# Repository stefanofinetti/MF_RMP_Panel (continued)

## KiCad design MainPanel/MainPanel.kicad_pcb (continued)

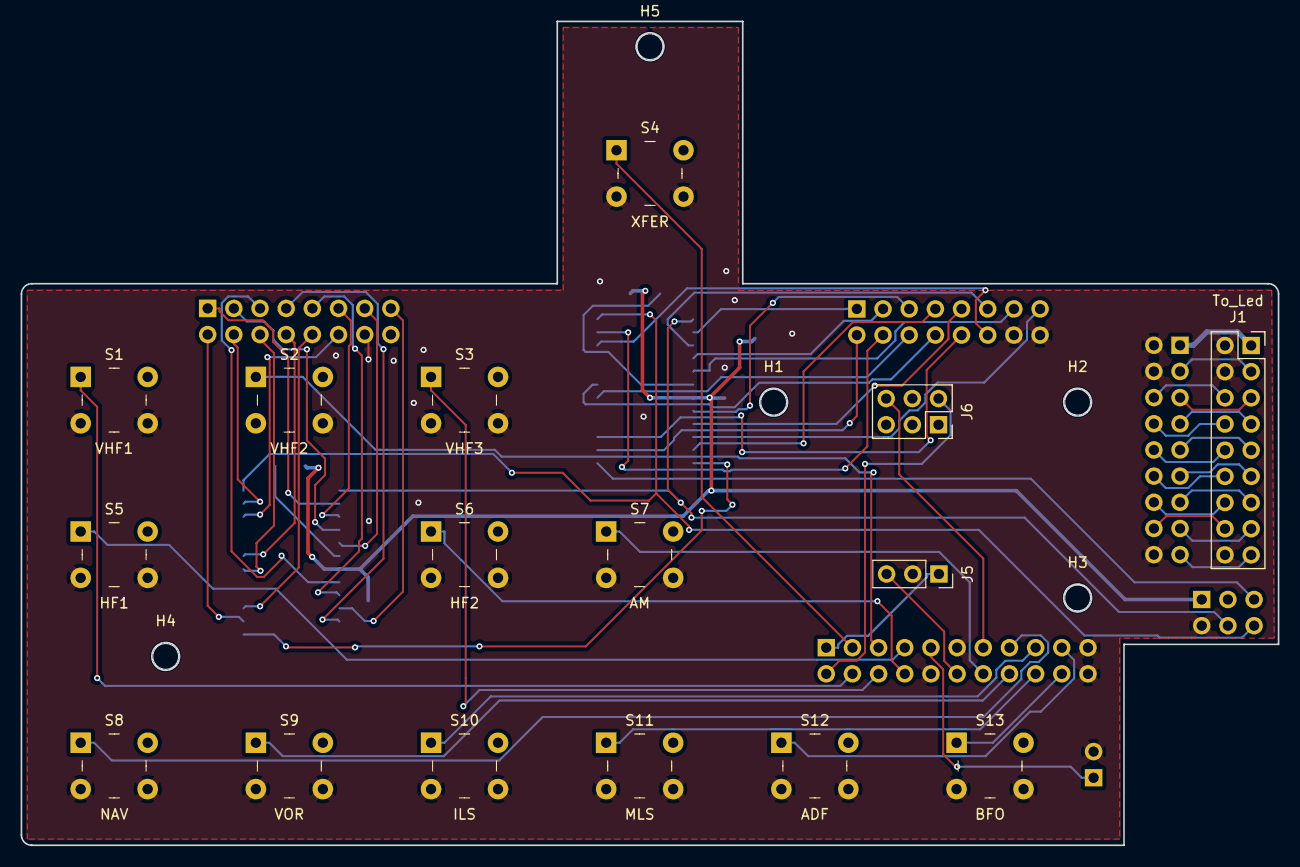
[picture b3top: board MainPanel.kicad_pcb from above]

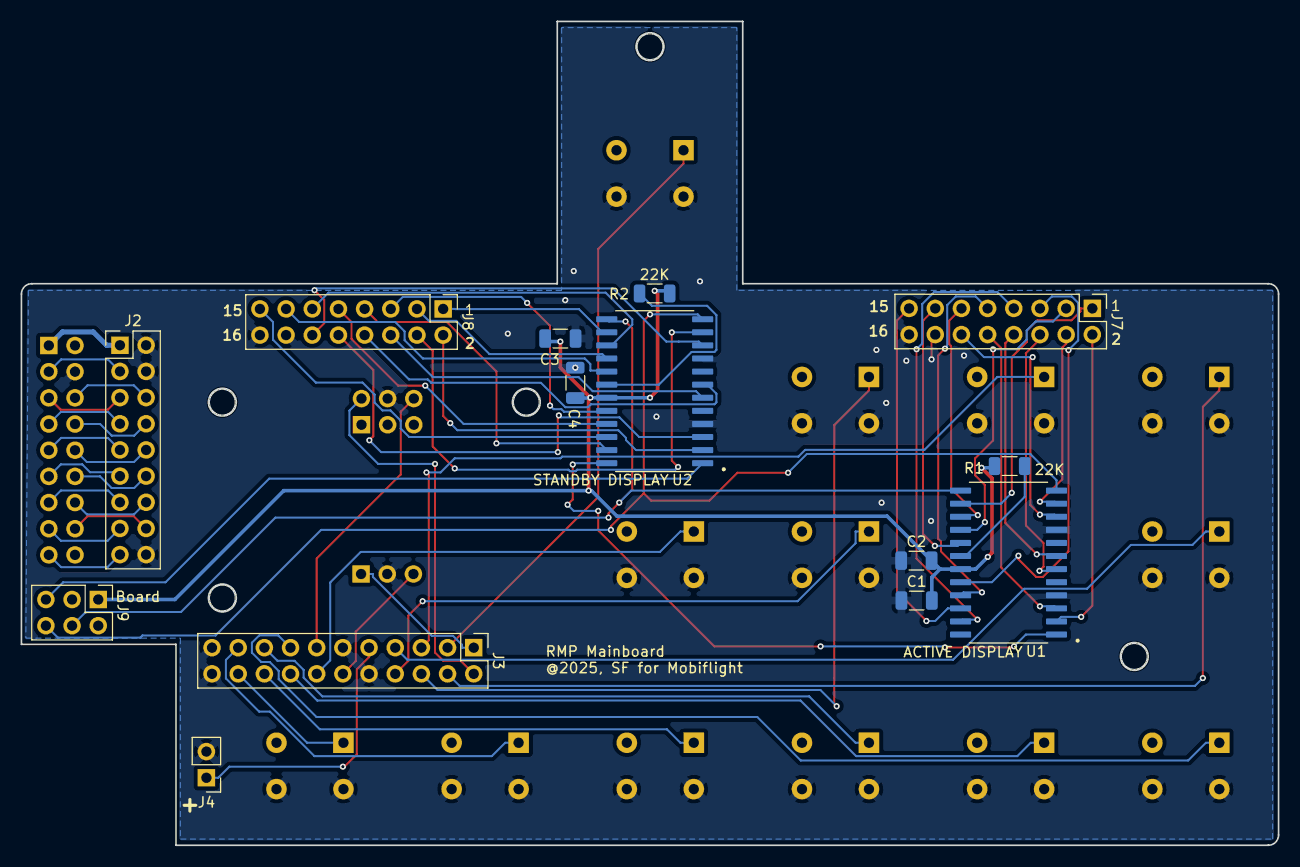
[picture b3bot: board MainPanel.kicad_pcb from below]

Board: 2 copper layers, 122.0 x 79.9 mm, 35 parts (14 on the bottom side), 69 nets.

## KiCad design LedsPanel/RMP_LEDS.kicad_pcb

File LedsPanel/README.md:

# RMP LedsPanel

The lighting board, right behind the front panel: the backlight of the
legends and the thirteen key lights. It plugs straight into the MainPanel.

* **PCB:** 122 × 80 mm, 2 layers, 1.6 mm, GND poured on both sides.
* **Fixing:** six M2.5 holes.
* **Parts:** 113. The backlight resistors and J1 are on the bottom.
* **Status:** built and in use. ERC, DRC and schematic parity are clean.

| Top: the panel side | Bottom: resistors and J1 |
|---|---|
|  |  |

Rendered by KiCad from the board file. The bottom is seen from below, so it
is mirrored against the top.

## Connector

| Ref | What | Goes to |
|---|---|---|
| J1 | Header 2 × 9, on the bottom | Plugs into the MainPanel's J1. 1 `+12V`, 2 / 4 / 18 GND, 3 backlight PWM, 5–17 the key LEDs |

## Backlight

69 orange 0805 LEDs, chosen to match the brightness of the Airbus panels,
on `+12V`:

* D1–D65: thirteen strings of five, each with its 75 Ω (R3–R15);
* D79–D82: one string of four, with R29, 75 Ω.

Every string returns to `LED_RETURN`, switched to GND by Q1, an IRLZ44N
(logic-level N-MOSFET, D2PAK). Its gate is driven by the backlight PWM
(D6) through R1, 100 Ω, with R2, 10 kΩ, pulling it down: with the PWM at 0
or the MobiFlight Connector closed, the backlight is off.

The string of four has one LED fewer across the same 75 Ω, so it carries
more current than the strings of five.

## Key lights

D66–D78, 3 mm flat-top LEDs, one in each key. The anode is driven straight
by the MCU pin through J1; the cathode goes to GND through 200 Ω
(R16–R28).

| D66 | D67 | D68 | D69 | D70 | D71 | D72 | D73 | D74 | D75 | D76 | D77 | D78 |
|---|---|---|---|---|---|---|---|---|---|---|---|---|
| VHF1 | VHF2 | VHF3 | HF1 | HF2 | AM | NAV | VOR | ILS | MLS | ADF | BFO | SEL |

The key lights are not dimmed. On the aircraft they follow the ANN LT
switch, apart from the backlight; a separate dimmer for them is being
considered.

## Assembly notes

* Everything is sized for hand soldering: 0805 LEDs, 1206 resistors.
* LED polarity, values and pin 1 are on the silkscreen.

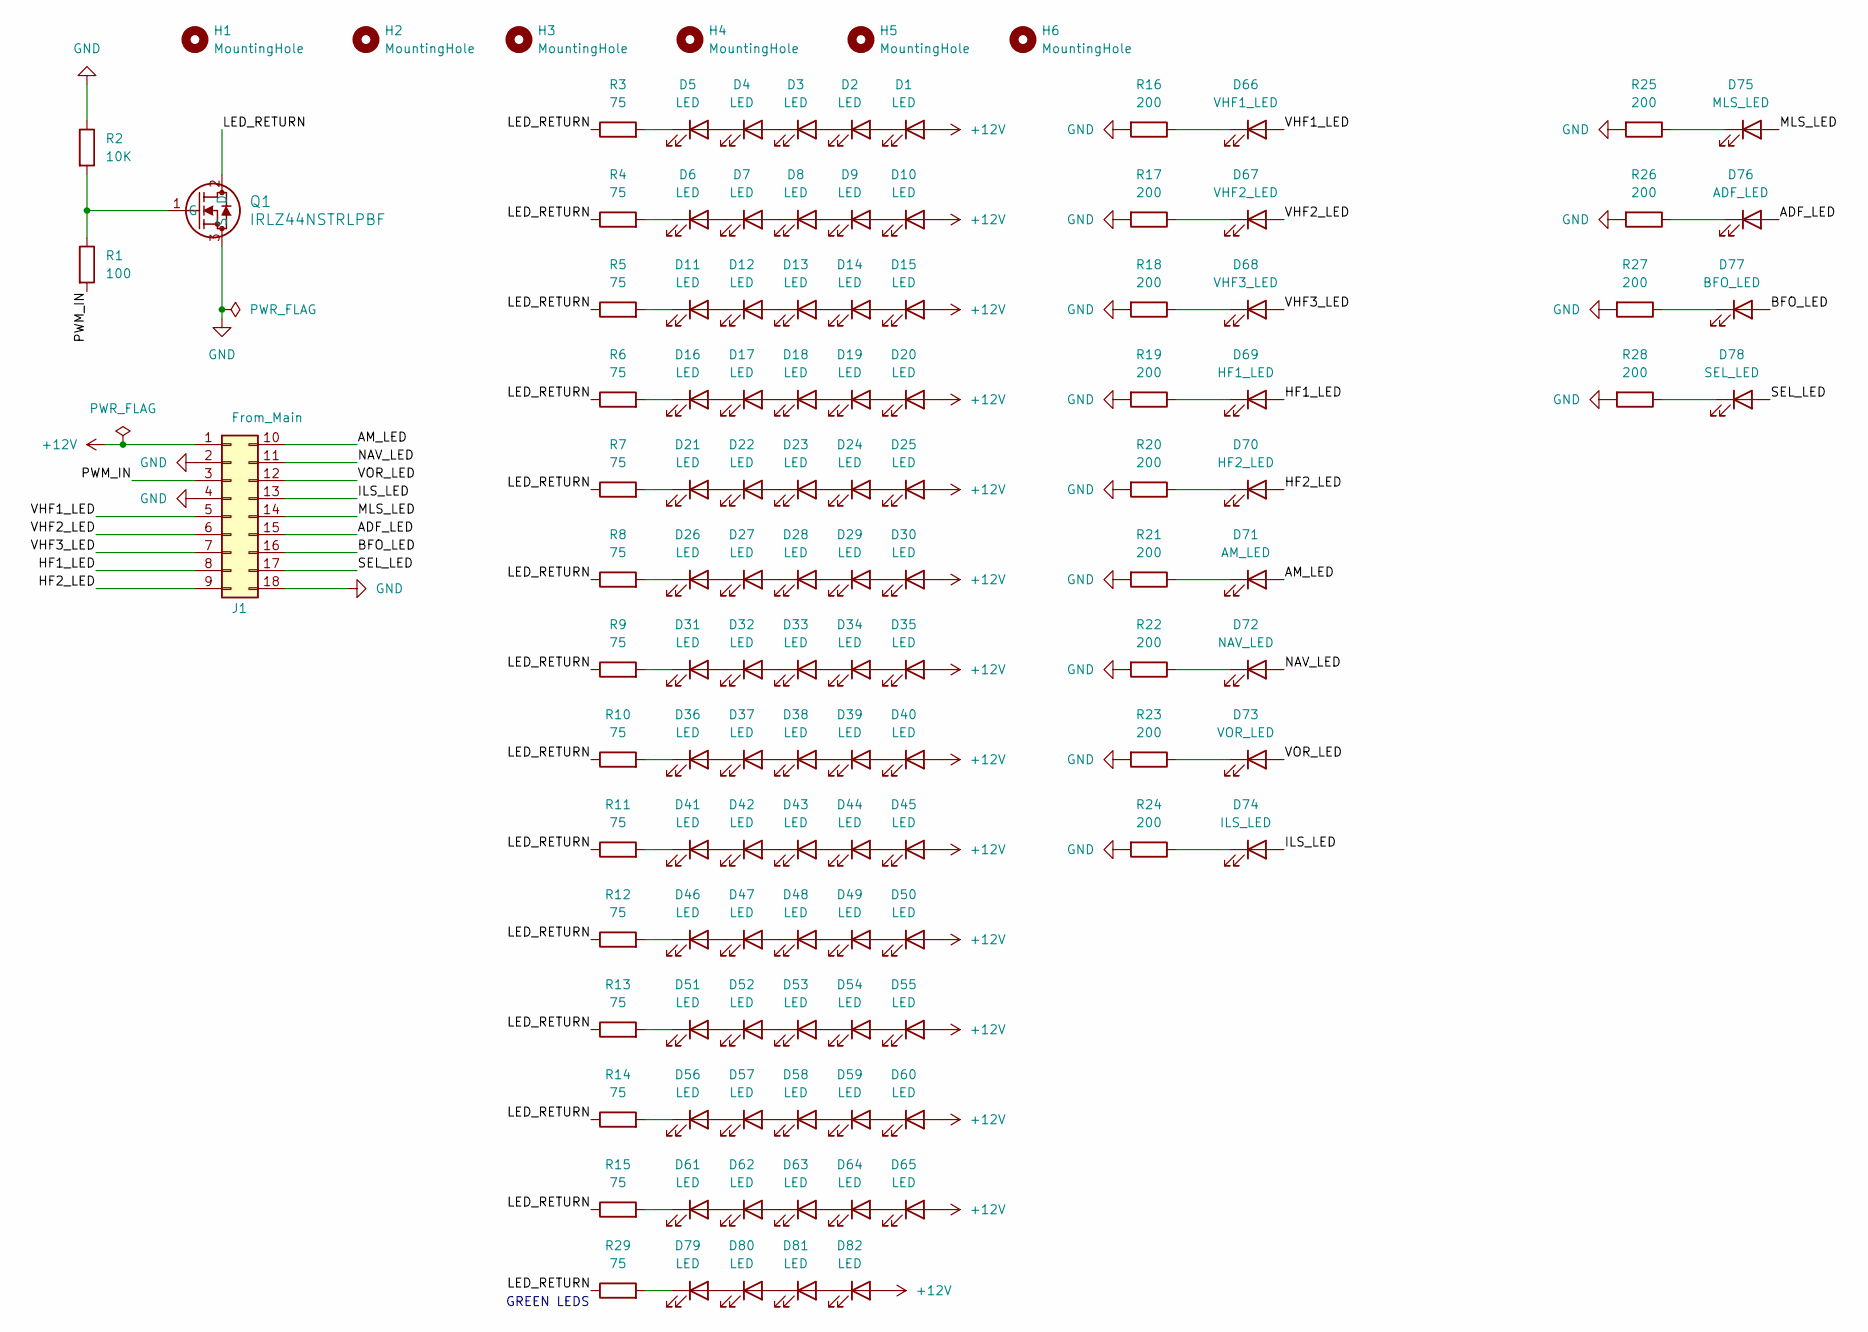
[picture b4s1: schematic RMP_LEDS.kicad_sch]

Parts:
D1, D2, D3, D4, D5, D6, D7, D8, D9, D10, D11, D12, D13, D14, D15, D16, D17, D18, D19, D20, D21, D22, D23, D24, D25, D26, D27, D28, D29, D30, D31, D32, D33, D34, D35, D36, D37, D38, D39, D40, D41, D42, D43, D44, D45, D46, D47, D48, D49, D50, D51, D52, D53, D54, D55, D56, D57, D58, D59, D60, D61, D62, D63, D64, D65, D79, D80, D81, D82: LED; LED_0805_2012Metric_Pad1.15x1.40mm_HandSolder
D66: VHF1_LED; LED_D3.0mm_FlatTop
D67: VHF2_LED; LED_D3.0mm_FlatTop
D68: VHF3_LED; LED_D3.0mm_FlatTop
D69: HF1_LED; LED_D3.0mm_FlatTop
D70: HF2_LED; LED_D3.0mm_FlatTop
D71: AM_LED; LED_D3.0mm_FlatTop
D72: NAV_LED; LED_D3.0mm_FlatTop
D73: VOR_LED; LED_D3.0mm_FlatTop
D74: ILS_LED; LED_D3.0mm_FlatTop
D75: MLS_LED; LED_D3.0mm_FlatTop
D76: ADF_LED; LED_D3.0mm_FlatTop
D77: BFO_LED; LED_D3.0mm_FlatTop
D78: SEL_LED; LED_D3.0mm_FlatTop
H1, H2, H3, H4, H5, H6: MountingHole; MountingHole_2.7mm_M2.5
J1: From_Main; PinHeader_2x09_P2.54mm_Vertical
Q1: IRLZ44NSTRLPBF; NMOSGDS_D2PAK_INF
R1: 100; R_1206_3216Metric_Pad1.30x1.75mm_HandSolder
R2: 10K; R_1206_3216Metric_Pad1.30x1.75mm_HandSolder
R3, R4, R5, R6, R7, R8, R9, R10, R11, R12, R13, R14, R15, R29: 75; R_1206_3216Metric_Pad1.30x1.75mm_HandSolder
R16, R17, R18, R19, R20, R21, R22, R23, R24, R25, R26, R27, R28: 200; R_1206_3216Metric_Pad1.30x1.75mm_HandSolder

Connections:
+12V: D1.2 (A), D10.2 (A), D15.2 (A), D20.2 (A), D25.2 (A), D30.2 (A), D35.2 (A), D40.2 (A), D45.2 (A), D50.2 (A), D55.2 (A), D60.2 (A), D65.2 (A), D82.2 (A), J1.1
/ADF_LED: D76.2 (A), J1.15
/AM_LED: D71.2 (A), J1.10
/BFO_LED: D77.2 (A), J1.16
/HF1_LED: D69.2 (A), J1.8
/HF2_LED: D70.2 (A), J1.9
/ILS_LED: D74.2 (A), J1.13
/LED_RETURN: Q1.2 (D), R3.1, R4.1, R5.1, R6.1, R7.1, R8.1, R9.1, R10.1, R11.1, R12.1, R13.1, R14.1, R15.1, R29.1
/MLS_LED: D75.2 (A), J1.14
/NAV_LED: D72.2 (A), J1.11
/PWM_IN: J1.3, R1.2
/SEL_LED: D78.2 (A), J1.17
/VHF1_LED: D66.2 (A), J1.5
/VHF2_LED: D67.2 (A), J1.6
/VHF3_LED: D68.2 (A), J1.7
/VOR_LED: D73.2 (A), J1.12
GND: J1.2, J1.4, J1.18, Q1.3 (S), R2.1, R16.2, R17.2, R18.2, R19.2, R20.2, R21.2, R22.2, R23.2, R24.2, R25.2, R26.2, R27.2, R28.2
unnamed: D1.1 (K), D2.2 (A)
unnamed: D2.1 (K), D3.2 (A)
unnamed: D3.1 (K), D4.2 (A)
unnamed: D4.1 (K), D5.2 (A)
unnamed: D5.1 (K), R3.2
unnamed: D6.2 (A), D7.1 (K)
unnamed: D6.1 (K), R4.2
unnamed: D7.2 (A), D8.1 (K)
unnamed: D8.2 (A), D9.1 (K)
unnamed: D9.2 (A), D10.1 (K)
unnamed: D11.2 (A), D12.1 (K)
unnamed: D11.1 (K), R5.2
unnamed: D12.2 (A), D13.1 (K)
unnamed: D13.2 (A), D14.1 (K)
unnamed: D14.2 (A), D15.1 (K)
unnamed: D16.2 (A), D17.1 (K)
unnamed: D16.1 (K), R6.2
unnamed: D17.2 (A), D18.1 (K)
unnamed: D18.2 (A), D19.1 (K)
unnamed: D19.2 (A), D20.1 (K)
unnamed: D21.2 (A), D22.1 (K)
unnamed: D21.1 (K), R7.2
unnamed: D22.2 (A), D23.1 (K)
unnamed: D23.2 (A), D24.1 (K)
unnamed: D24.2 (A), D25.1 (K)
unnamed: D26.2 (A), D27.1 (K)
unnamed: D26.1 (K), R8.2
unnamed: D27.2 (A), D28.1 (K)
unnamed: D28.2 (A), D29.1 (K)
unnamed: D29.2 (A), D30.1 (K)
unnamed: D31.2 (A), D32.1 (K)
unnamed: D31.1 (K), R9.2
unnamed: D32.2 (A), D33.1 (K)
unnamed: D33.2 (A), D34.1 (K)
unnamed: D34.2 (A), D35.1 (K)
unnamed: D36.2 (A), D37.1 (K)
unnamed: D36.1 (K), R10.2
unnamed: D37.2 (A), D38.1 (K)
unnamed: D38.2 (A), D39.1 (K)
unnamed: D39.2 (A), D40.1 (K)
unnamed: D41.2 (A), D42.1 (K)
unnamed: D41.1 (K), R11.2
unnamed: D42.2 (A), D43.1 (K)
unnamed: D43.2 (A), D44.1 (K)
unnamed: D44.2 (A), D45.1 (K)
unnamed: D46.2 (A), D47.1 (K)
unnamed: D46.1 (K), R12.2
unnamed: D47.2 (A), D48.1 (K)
unnamed: D48.2 (A), D49.1 (K)
unnamed: D49.2 (A), D50.1 (K)
unnamed: D51.2 (A), D52.1 (K)
unnamed: D51.1 (K), R13.2
unnamed: D52.2 (A), D53.1 (K)
unnamed: D53.2 (A), D54.1 (K)
unnamed: D54.2 (A), D55.1 (K)
unnamed: D56.2 (A), D57.1 (K)
unnamed: D56.1 (K), R14.2
unnamed: D57.2 (A), D58.1 (K)
unnamed: D58.2 (A), D59.1 (K)
unnamed: D59.2 (A), D60.1 (K)
unnamed: D61.2 (A), D62.1 (K)
unnamed: D61.1 (K), R15.2
unnamed: D62.2 (A), D63.1 (K)
unnamed: D63.2 (A), D64.1 (K)
unnamed: D64.2 (A), D65.1 (K)
unnamed: D66.1 (K), R16.1
unnamed: D67.1 (K), R17.1
unnamed: D68.1 (K), R18.1
unnamed: D69.1 (K), R19.1
unnamed: D70.1 (K), R20.1
unnamed: D71.1 (K), R21.1
unnamed: D72.1 (K), R22.1
unnamed: D73.1 (K), R23.1
unnamed: D74.1 (K), R24.1
unnamed: D75.1 (K), R25.1
unnamed: D76.1 (K), R26.1
unnamed: D77.1 (K), R27.1
unnamed: D78.1 (K), R28.1
unnamed: D79.2 (A), D80.1 (K)
unnamed: D79.1 (K), R29.2
unnamed: D80.2 (A), D81.1 (K)
unnamed: D81.2 (A), D82.1 (K)
unnamed: Q1.1 (G), R1.1, R2.2

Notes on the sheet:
GREEN LEDS

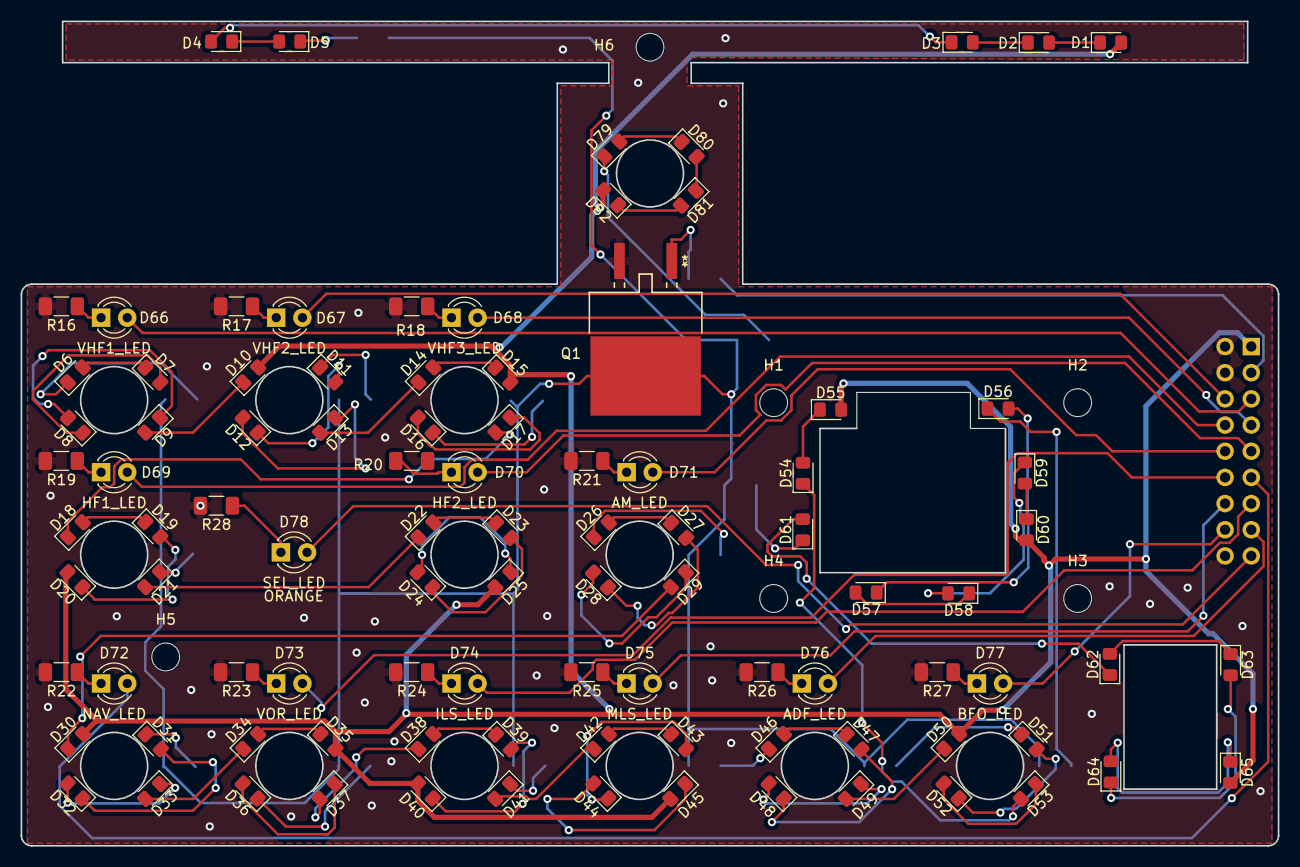
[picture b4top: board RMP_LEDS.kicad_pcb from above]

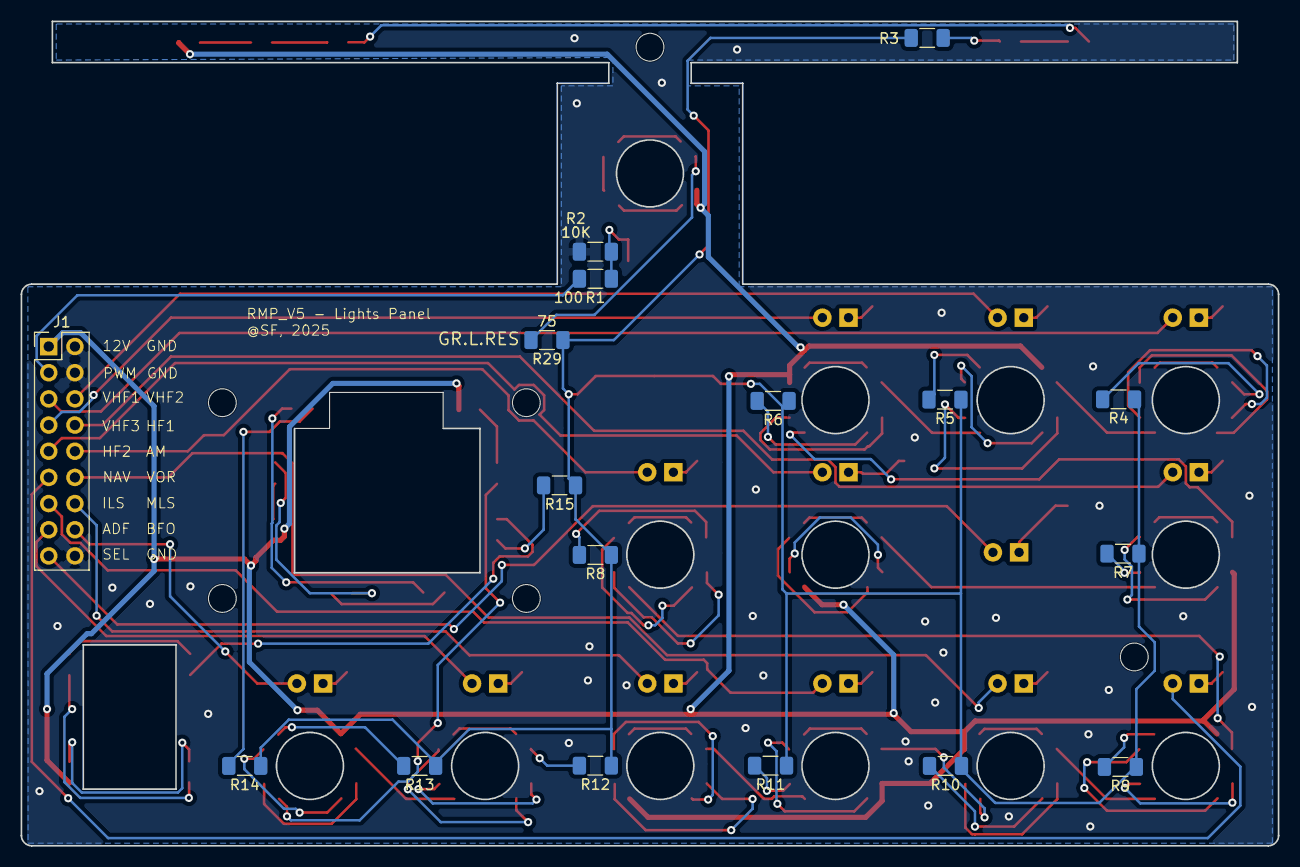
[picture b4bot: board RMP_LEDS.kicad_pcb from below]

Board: 2 copper layers, 122.0 x 80.0 mm, 119 parts (17 on the bottom side), 100 nets.

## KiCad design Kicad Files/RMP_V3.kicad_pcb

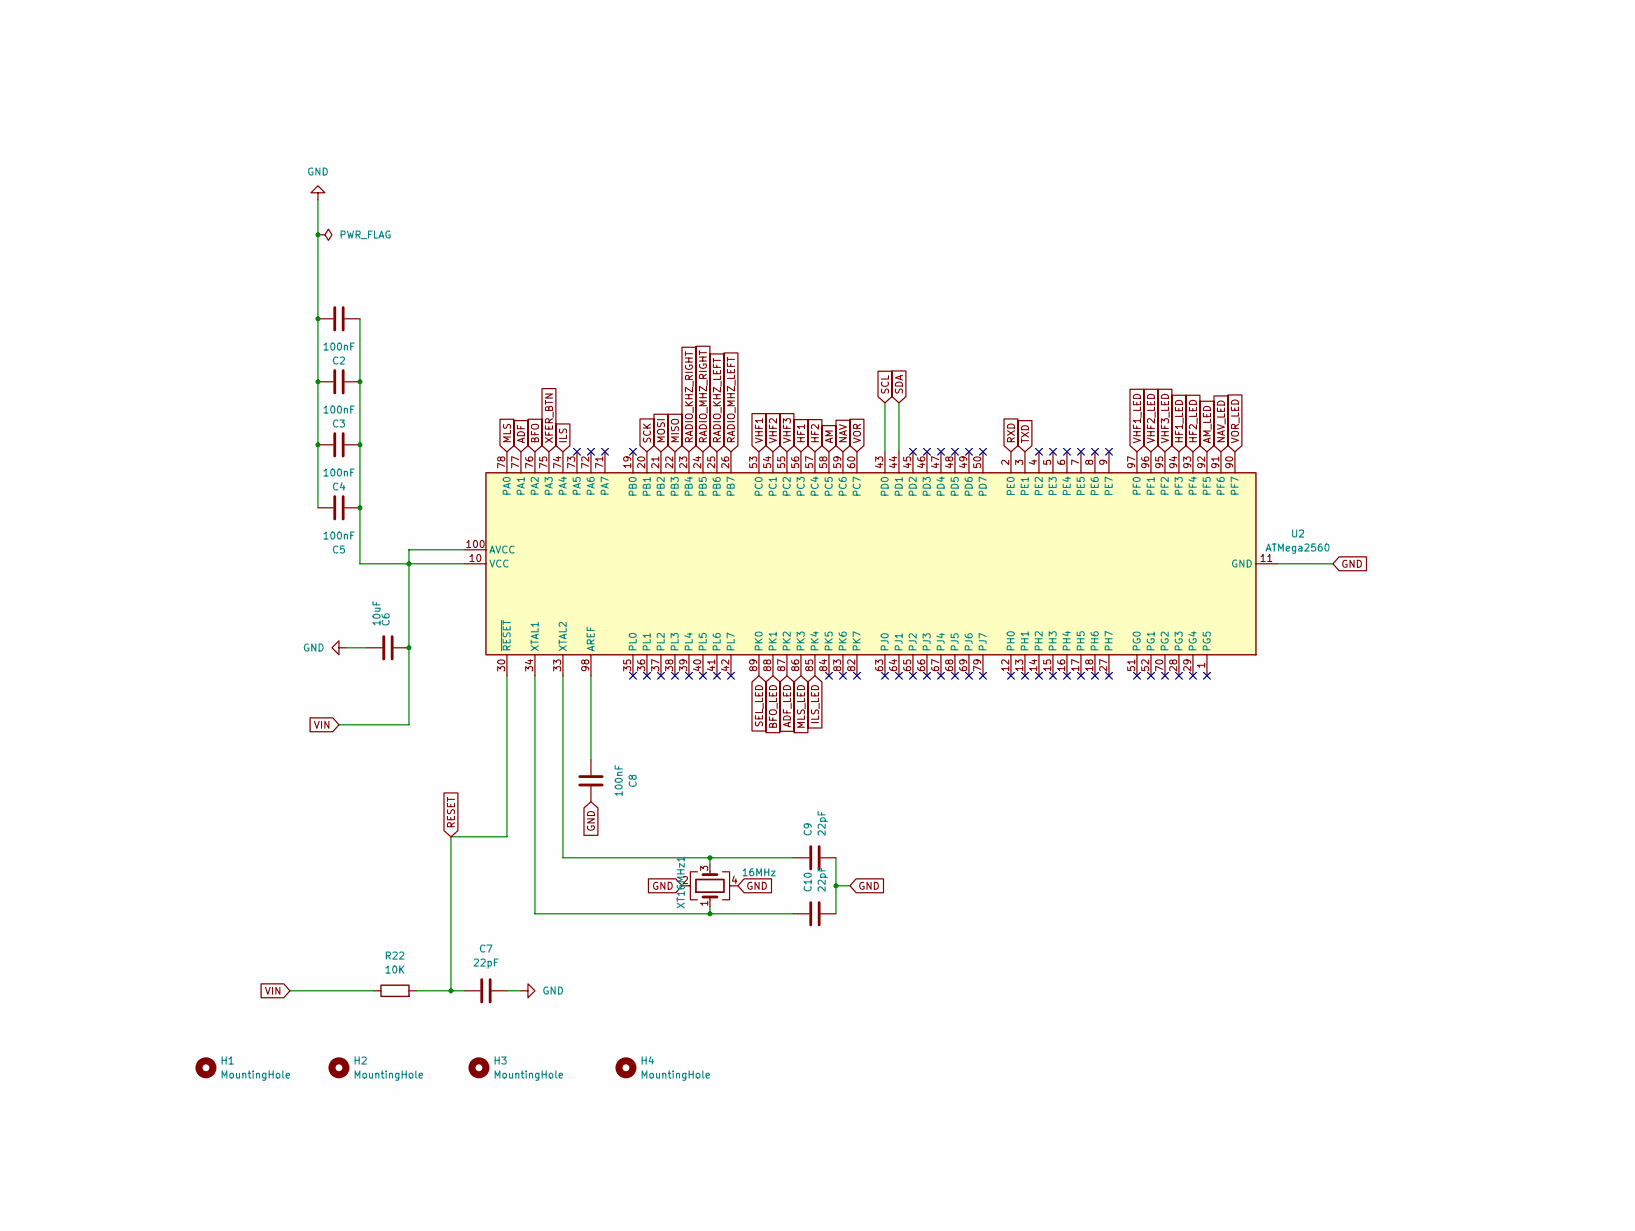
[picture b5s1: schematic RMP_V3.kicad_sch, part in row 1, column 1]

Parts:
C2, C3, C4, C5, C8: 100nF; C_1206_3216Metric_Pad1.33x1.80mm_HandSolder
C6: 10uF; C_1206_3216Metric_Pad1.33x1.80mm_HandSolder
C7, C9, C10: 22pF; C_1206_3216Metric_Pad1.33x1.80mm_HandSolder
H1, H2, H3, H4: MountingHole; MountingHole_3.2mm_M3
R22: 10K; R_1206_3216Metric_Pad1.30x1.75mm_HandSolder
U2: ATMega2560; TQFP-100_14x14mm_P0.5mm
XT16MHz1: 16MHz; Crystal_SMD_EuroQuartz_MJ-4Pin_5.0x3.2mm_HandSoldering

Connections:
ADF: U2.77 (PA1); also elsewhere on the board
ADF_LED: U2.87 (PK2); also elsewhere on the board
AM: U2.58 (PC5); also elsewhere on the board
AM_LED: U2.92 (PF5); also elsewhere on the board
BFO: U2.76 (PA2); also elsewhere on the board
BFO_LED: U2.88 (PK1); also elsewhere on the board
GND: C2.2, C3.2, C4.2, C5.2, C6.2, C7.2, C8.2, C9.2, C10.2, U2.11 (GND), U2.32 (GND), U2.62 (GND), U2.81 (GND), U2.99 (GND), XT16MHz1.2, XT16MHz1.4; also elsewhere on the board
HF1: U2.56 (PC3); also elsewhere on the board
HF1_LED: U2.94 (PF3); also elsewhere on the board
HF2: U2.57 (PC4); also elsewhere on the board
HF2_LED: U2.93 (PF4); also elsewhere on the board
ILS: U2.74 (PA4); also elsewhere on the board
ILS_LED: U2.85 (PK4); also elsewhere on the board
MISO: U2.22 (PB3); also elsewhere on the board
MLS: U2.78 (PA0); also elsewhere on the board
MLS_LED: U2.86 (PK3); also elsewhere on the board
MOSI: U2.21 (PB2); also elsewhere on the board
NAV: U2.59 (PC6); also elsewhere on the board
NAV_LED: U2.91 (PF6); also elsewhere on the board
unnamed: C8.1, U2.98 (AREF)
unnamed: C10.1, U2.34 (XTAL1), XT16MHz1.1
unnamed: C9.1, U2.33 (XTAL2), XT16MHz1.3
RADIO_KHZ_LEFT: U2.25 (PB6); also elsewhere on the board
RADIO_KHZ_RIGHT: U2.23 (PB4); also elsewhere on the board
RADIO_MHZ_LEFT: U2.26 (PB7); also elsewhere on the board
RADIO_MHZ_RIGHT: U2.24 (PB5); also elsewhere on the board
RESET: C7.1, R22.2, U2.30 (~RESET); also elsewhere on the board
RXD: U2.2 (PE0); also elsewhere on the board
SCK: U2.20 (PB1); also elsewhere on the board
SCL: U2.43 (PD0); also elsewhere on the board
SDA: U2.44 (PD1); also elsewhere on the board
SEL_LED: U2.89 (PK0); also elsewhere on the board
TXD: U2.3 (PE1); also elsewhere on the board
VHF1: U2.53 (PC0); also elsewhere on the board
VHF1_LED: U2.97 (PF0); also elsewhere on the board
VHF2: U2.54 (PC1); also elsewhere on the board
VHF2_LED: U2.96 (PF1); also elsewhere on the board
VHF3: U2.55 (PC2); also elsewhere on the board
VHF3_LED: U2.95 (PF2); also elsewhere on the board
VIN: C2.1, C3.1, C4.1, C5.1, C6.1, R22.1, U2.10 (VCC), U2.31 (VCC), U2.61 (VCC), U2.80 (VCC), U2.100 (AVCC); also elsewhere on the board
VOR: U2.60 (PC7); also elsewhere on the board
VOR_LED: U2.90 (PF7); also elsewhere on the board
XFER_BTN: U2.75 (PA3); also elsewhere on the board

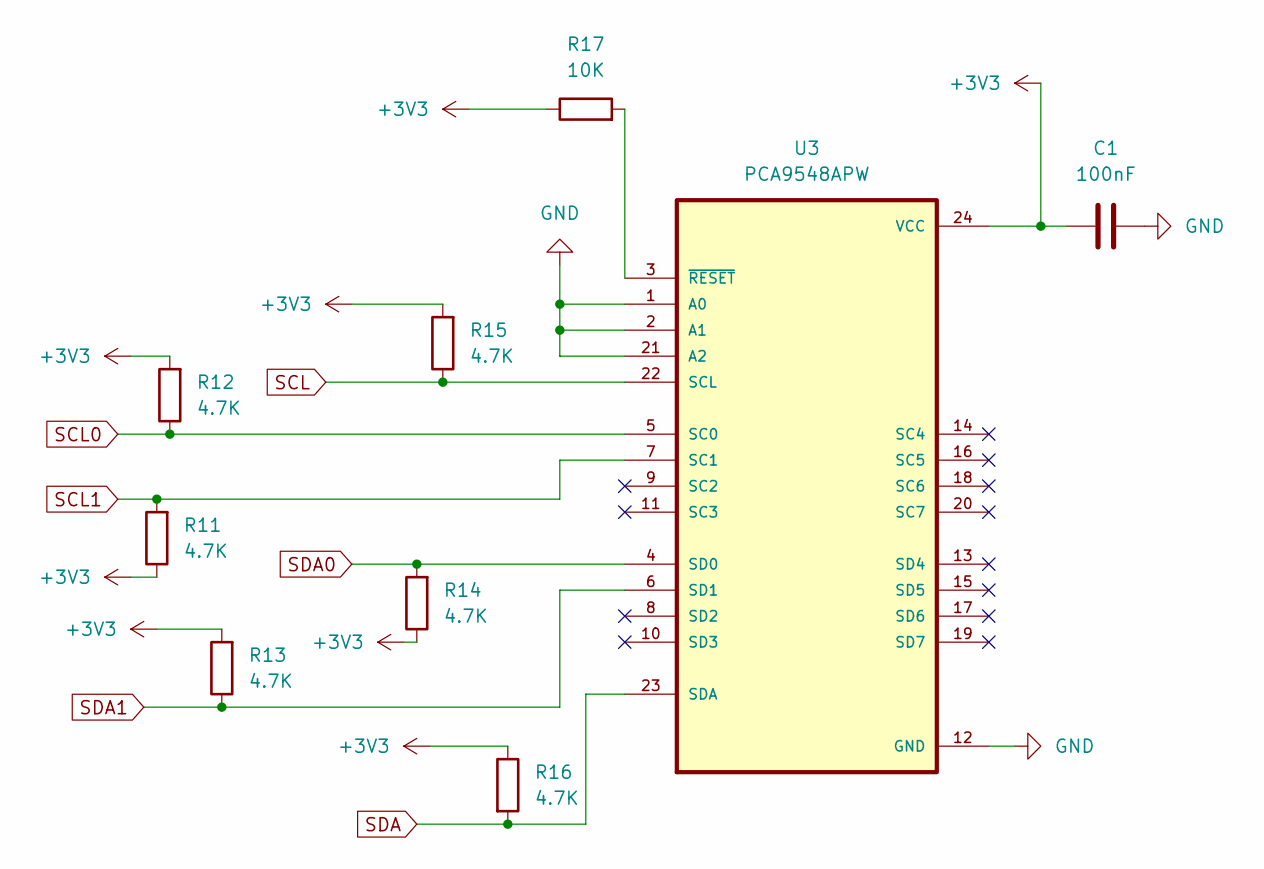
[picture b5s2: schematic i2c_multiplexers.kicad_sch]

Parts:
C1: 100nF; C_1206_3216Metric_Pad1.33x1.80mm_HandSolder
R11, R12, R13, R14, R15, R16: 4.7K; R_1206_3216Metric_Pad1.30x1.75mm_HandSolder
R17: 10K; R_1206_3216Metric_Pad1.30x1.75mm_HandSolder
U3: PCA9548APW; SOP65P640X120-24N

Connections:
+3V3: C1.1, R11.1, R12.2, R13.2, R14.1, R15.2, R16.1, R17.1, U3.24 (VCC); also elsewhere on the board
GND: C1.2, U3.1 (A0), U3.2 (A1), U3.12 (GND), U3.21 (A2); also elsewhere on the board
unnamed: R17.2, U3.3 (~RESET)
SCL: R15.1, U3.22 (SCL); also elsewhere on the board
SCL0: R12.1, U3.5 (SC0); also elsewhere on the board
SCL1: R11.2, U3.7 (SC1); also elsewhere on the board
SDA: R16.2, U3.23 (SDA); also elsewhere on the board
SDA0: R14.2, U3.4 (SD0); also elsewhere on the board
SDA1: R13.1, U3.6 (SD1); also elsewhere on the board

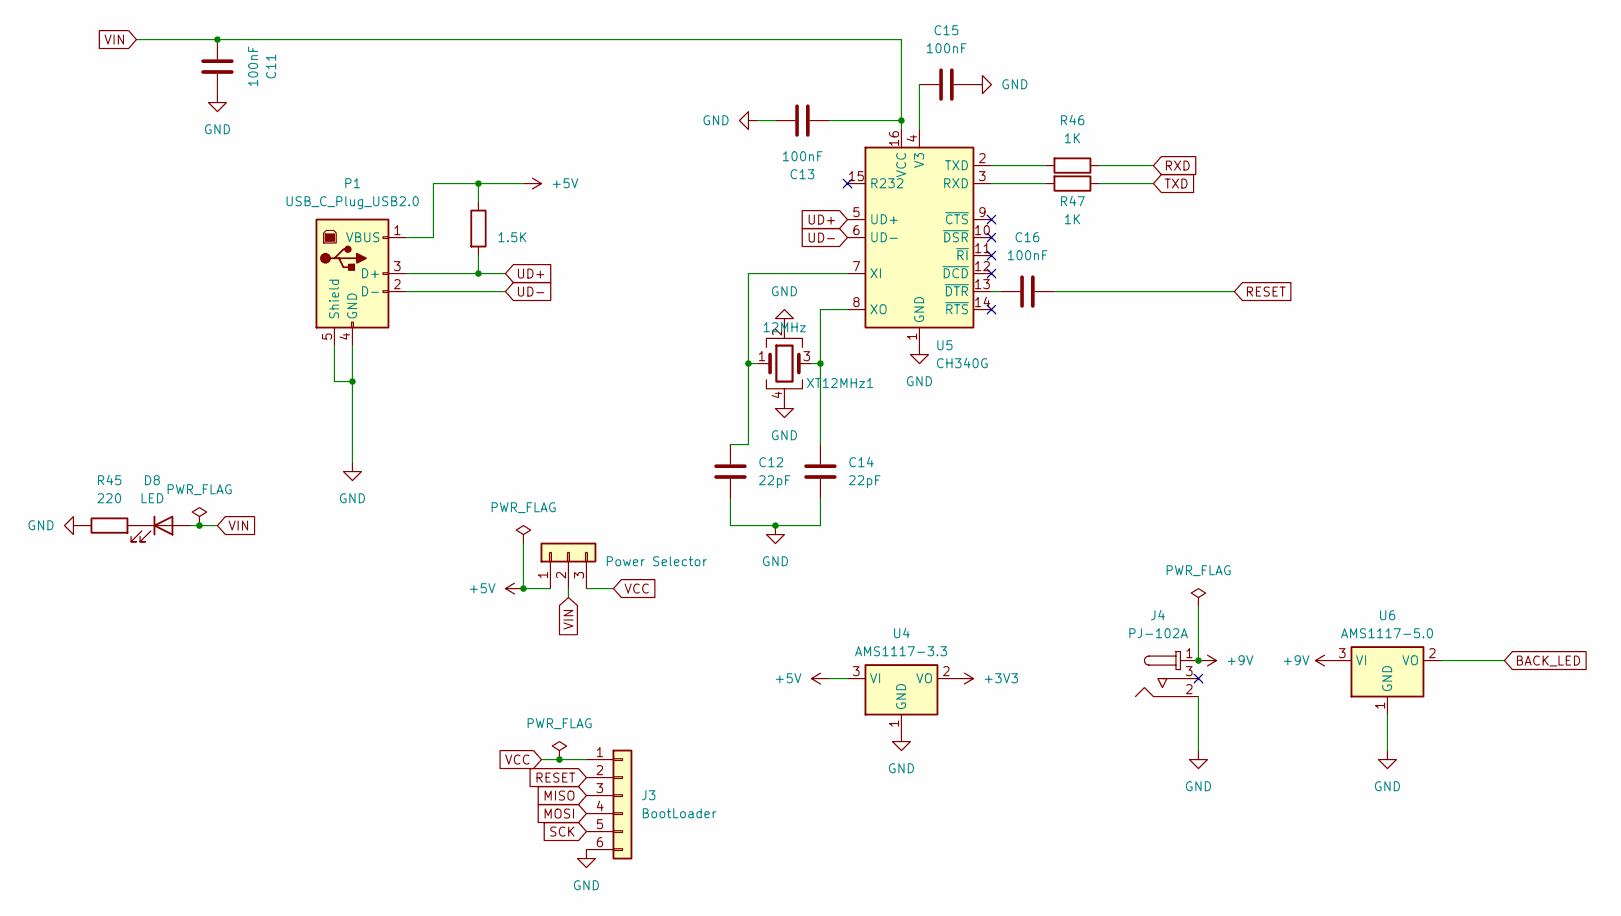
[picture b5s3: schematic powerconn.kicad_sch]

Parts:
C11, C13, C15, C16: 100nF; C_1206_3216Metric_Pad1.33x1.80mm_HandSolder
C12, C14: 22pF; C_1206_3216Metric_Pad1.33x1.80mm_HandSolder
D8: LED; LED_1206_3216Metric_Pad1.42x1.75mm_HandSolder
J3: BootLoader; PinHeader_1x06_P2.54mm_Vertical
J4: PJ-102A; Barrel_Jack_5.5mmODx2.1mmID_PJ-102A; MPN PJ-102A; Digi-Key_PN CP-102A-ND
JP1: Power Selector; PinHeader_1x03_P2.54mm_Vertical
P1: USB_C_Plug_USB2.0; USB_B_OST_USB-B1HSxx_Horizontal
R45: 220; R_1206_3216Metric_Pad1.30x1.75mm_HandSolder
R46, R47: 1K; R_1206_3216Metric_Pad1.30x1.75mm_HandSolder
R48: 1.5K; R_1206_3216Metric_Pad1.30x1.75mm_HandSolder
U4: AMS1117-3.3; SOT-223-3_TabPin2
U5: CH340G; SOIC-16_3.9x9.9mm_P1.27mm
U6: AMS1117-5.0; SOT-223-3_TabPin2
XT12MHz1: 12MHz; Crystal_SMD_EuroQuartz_MJ-4Pin_5.0x3.2mm_HandSoldering

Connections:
+3V3: U4.2 (VO); also elsewhere on the board
+5V: JP1.1, P1.1 (VBUS), R48.1, U4.3 (VI)
+9V: J4.1, U6.3 (VI)
BACK_LED: U6.2 (VO); also elsewhere on the board
GND: C11.2, C12.1, C13.2, C14.1, C15.2, J3.6, J4.2, P1.4 (GND), P1.5 (Shield), R45.1, U4.1 (GND), U5.1 (GND), U6.1 (GND), XT12MHz1.2, XT12MHz1.4; also elsewhere on the board
MISO: J3.3; also elsewhere on the board
MOSI: J3.4; also elsewhere on the board
unnamed: D8.1 (K), R45.2
unnamed: R47.2, U5.3 (RXD)
unnamed: R46.2, U5.2 (TXD)
unnamed: C15.1, U5.4 (V3)
unnamed: C12.2, U5.7 (XI), XT12MHz1.1
unnamed: C14.2, U5.8 (XO), XT12MHz1.3
unnamed: C16.1, U5.13 (~DTR)
RESET: C16.2, J3.2; also elsewhere on the board
RXD: R46.1; also elsewhere on the board
SCK: J3.5; also elsewhere on the board
TXD: R47.1; also elsewhere on the board
UD+: P1.3 (D+), R48.2, U5.5 (UD+)
UD-: P1.2 (D-), U5.6 (UD-)
VCC: J3.1, JP1.3
VIN: C11.1, C13.1, D8.2 (A), JP1.2, U5.16 (VCC); also elsewhere on the board

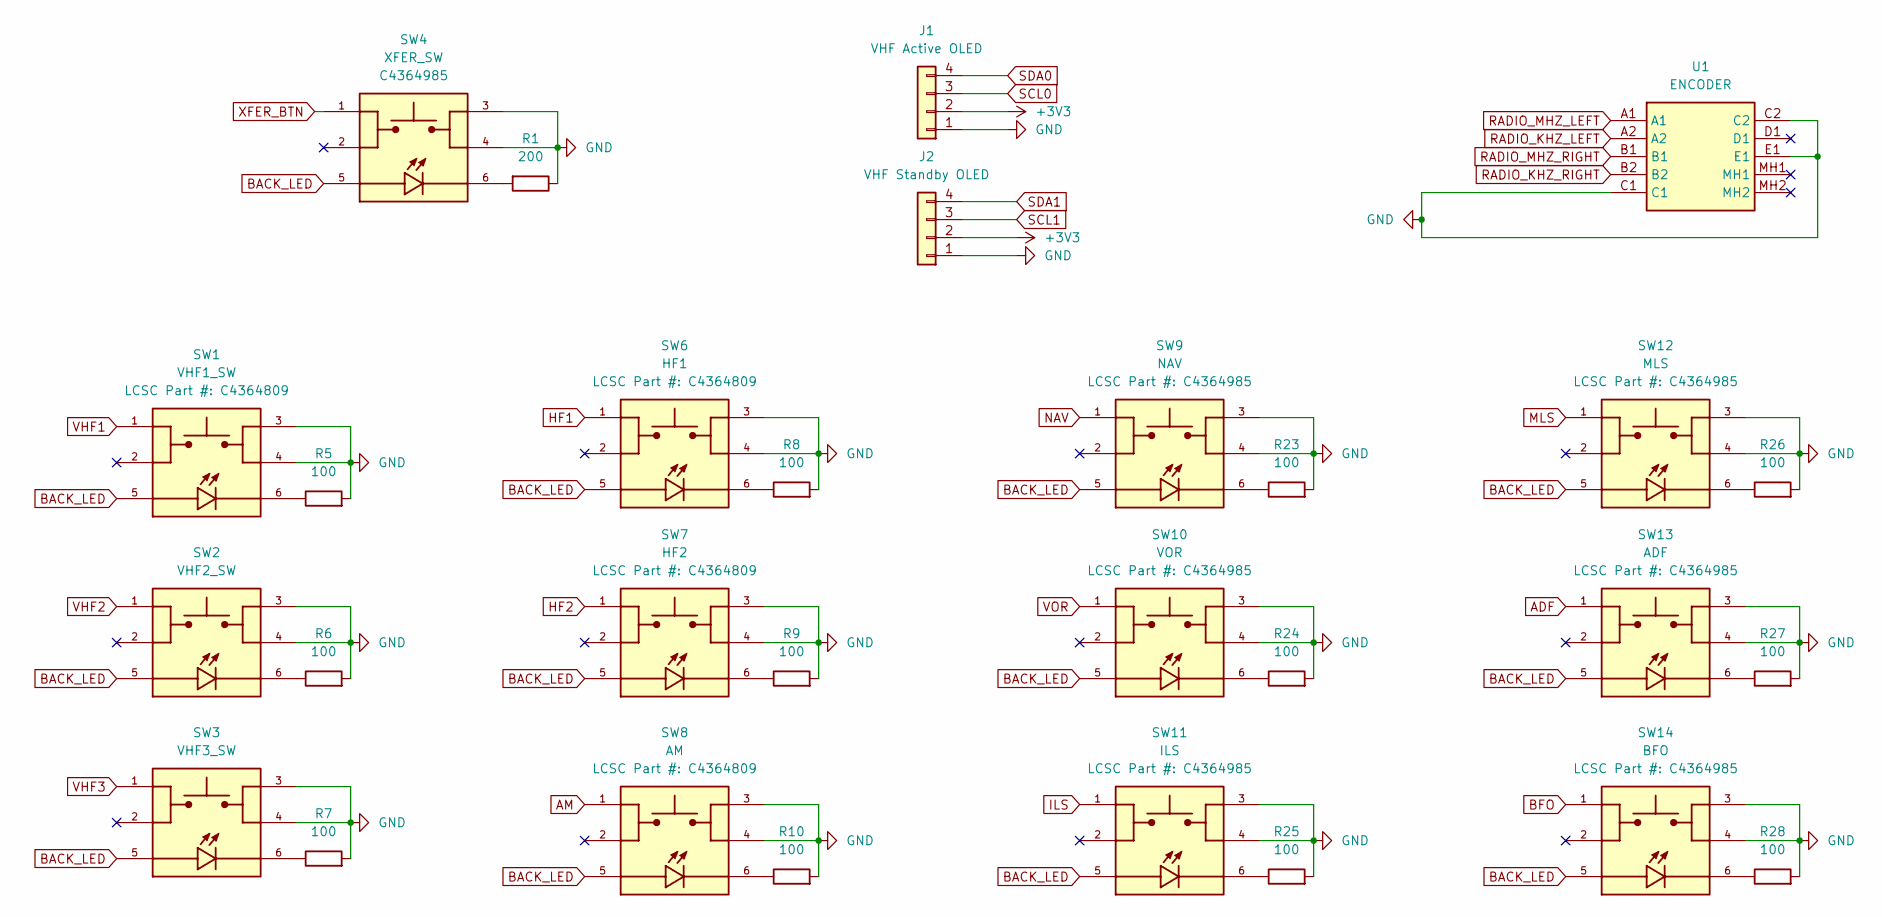
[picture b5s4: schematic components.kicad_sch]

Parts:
J1: VHF Active OLED; PinSocket_1x04_P2.54mm_Vertical
J2: VHF Standby OLED; PinSocket_1x04_P2.54mm_Vertical
R1: 200; R_1206_3216Metric_Pad1.30x1.75mm_HandSolder
R5, R6, R7, R8, R9, R10, R23, R24, R25, R26, R27, R28: 100; R_1206_3216Metric_Pad1.30x1.75mm_HandSolder
SW1: VHF1_SW; SW_TL3240F260R; PARTREV D; LCSC Part # C4364809
SW2: VHF2_SW; SW_TL3240F260R; PARTREV D; LCSC Part # C4364809
SW3: VHF3_SW; SW_TL3240F260R; PARTREV D; LCSC Part # C4364809
SW4: XFER_SW; SW_TL3240F260R; PARTREV D; LCSC Part # C4364985
SW6: HF1; SW_TL3240F260R; PARTREV D; LCSC Part # C4364809
SW7: HF2; SW_TL3240F260R; PARTREV D; LCSC Part # C4364809
SW8: AM; SW_TL3240F260R; PARTREV D; LCSC Part # C4364809
SW9: NAV; SW_TL3240F260R; PARTREV D; LCSC Part # C4364985
SW10: VOR; SW_TL3240F260R; PARTREV D; LCSC Part # C4364985
SW11: ILS; SW_TL3240F260R; PARTREV D; LCSC Part # C4364985
SW12: MLS; SW_TL3240F260R; PARTREV D; LCSC Part # C4364985
SW13: ADF; SW_TL3240F260R; PARTREV D; LCSC Part # C4364985
SW14: BFO; SW_TL3240F260R; PARTREV D; LCSC Part # C4364985
U1: ENCODER; EC11EBB24C03; Manufacturer_Part_Number EC11EBB24C03; Mouser Part Number 688-EC11EBB24C03

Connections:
+3V3: J1.2, J2.2; also elsewhere on the board
ADF: SW13.1; also elsewhere on the board
AM: SW8.1; also elsewhere on the board
BACK_LED: SW1.5, SW2.5, SW3.5, SW4.5, SW6.5, SW7.5, SW8.5, SW9.5, SW10.5, SW11.5, SW12.5, SW13.5, SW14.5; also elsewhere on the board
BFO: SW14.1; also elsewhere on the board
GND: J1.1, J2.1, R1.1, R5.2, R6.2, R7.2, R8.2, R9.2, R10.2, R23.2, R24.2, R25.2, R26.2, R27.2, R28.2, SW1.3, SW1.4, SW2.3, SW2.4, SW3.3, SW3.4, SW4.3, SW4.4, SW6.3, SW6.4, SW7.3, SW7.4, SW8.3, SW8.4, SW9.3, SW9.4, SW10.3, SW10.4, SW11.3, SW11.4, SW12.3, SW12.4, SW13.3, SW13.4, SW14.3, SW14.4, U1.C1, U1.C2, U1.E1; also elsewhere on the board
HF1: SW6.1; also elsewhere on the board
HF2: SW7.1; also elsewhere on the board
ILS: SW11.1; also elsewhere on the board
MLS: SW12.1; also elsewhere on the board
NAV: SW9.1; also elsewhere on the board
unnamed: R1.2, SW4.6
unnamed: R5.1, SW1.6
unnamed: R6.1, SW2.6
unnamed: R7.1, SW3.6
unnamed: R8.1, SW6.6
unnamed: R9.1, SW7.6
unnamed: R10.1, SW8.6
unnamed: R23.1, SW9.6
unnamed: R24.1, SW10.6
unnamed: R25.1, SW11.6
unnamed: R26.1, SW12.6
unnamed: R27.1, SW13.6
unnamed: R28.1, SW14.6
RADIO_KHZ_LEFT: U1.A2; also elsewhere on the board
RADIO_KHZ_RIGHT: U1.B2; also elsewhere on the board
RADIO_MHZ_LEFT: U1.A1; also elsewhere on the board
RADIO_MHZ_RIGHT: U1.B1; also elsewhere on the board
SCL0: J1.3; also elsewhere on the board
SCL1: J2.3; also elsewhere on the board
SDA0: J1.4; also elsewhere on the board
SDA1: J2.4; also elsewhere on the board
VHF1: SW1.1; also elsewhere on the board
VHF2: SW2.1; also elsewhere on the board
VHF3: SW3.1; also elsewhere on the board
VOR: SW10.1; also elsewhere on the board
XFER_BTN: SW4.1; also elsewhere on the board
